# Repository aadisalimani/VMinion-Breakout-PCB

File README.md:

# VMinion Breakout PCB

This project is focused on creating a PCB that simplifies connections on the Ratrig VMinion. Although designed be me, it is inspired by the divider PCB mod by Vector3D [here](https://github.com/AdamV3D/RR-V-Minion-Mods/tree/main/V3D%20Divider%20PCB). 

## :warning: Beta Version :warning:
Please note that the "VMinion Breakout PCB" is currently in a **beta phase**. It's constantly being updated and improved. Use this mod at your own risk. The rest of the parts (printed casing, mounting parts, etc.) will come soon.

## Open Source
Everything related to this project will be open-source. Contributions, suggestions, and improvements are always welcome.

## Bill of Materials (BOM)
A work-in-progress BOM is available [here](https://docs.google.com/spreadsheets/d/1l2unTY74QwLAbzYWbJA4JIBaFDDriVfRlH6mz4mGnKs/edit?usp=sharing).

## Getting Started
*Features*

Unlike other breakout boards, this has a plethora of ports to fit almost any configuration:

- 4x Motor Ports
- 5x General Ports (Endstop, Servo, Neopixel etc.)
- 1x Probe Port (5v or 24v with diode)
- 3x Fan Ports (Selectable Voltage) - Two Ports Share Selected Voltage
- 1x ADXL Port
- 2x Therm Ports
- 1x Hotend Port (Max ~120W)
- 1x Bed Port (Max ~180W)
- 1x 24v Step Down To 12v (K78L12-500R3)

Uses 2x 2x9 Microfit And 1x Plugable Terminal Block

*Instrucions will follow soon*

## PCB Images

## License
This PCB project is licensed under the Creative Commons Attribution-NonCommercial 4.0 International License - see the [LICENSE](LICENSE) file for details.

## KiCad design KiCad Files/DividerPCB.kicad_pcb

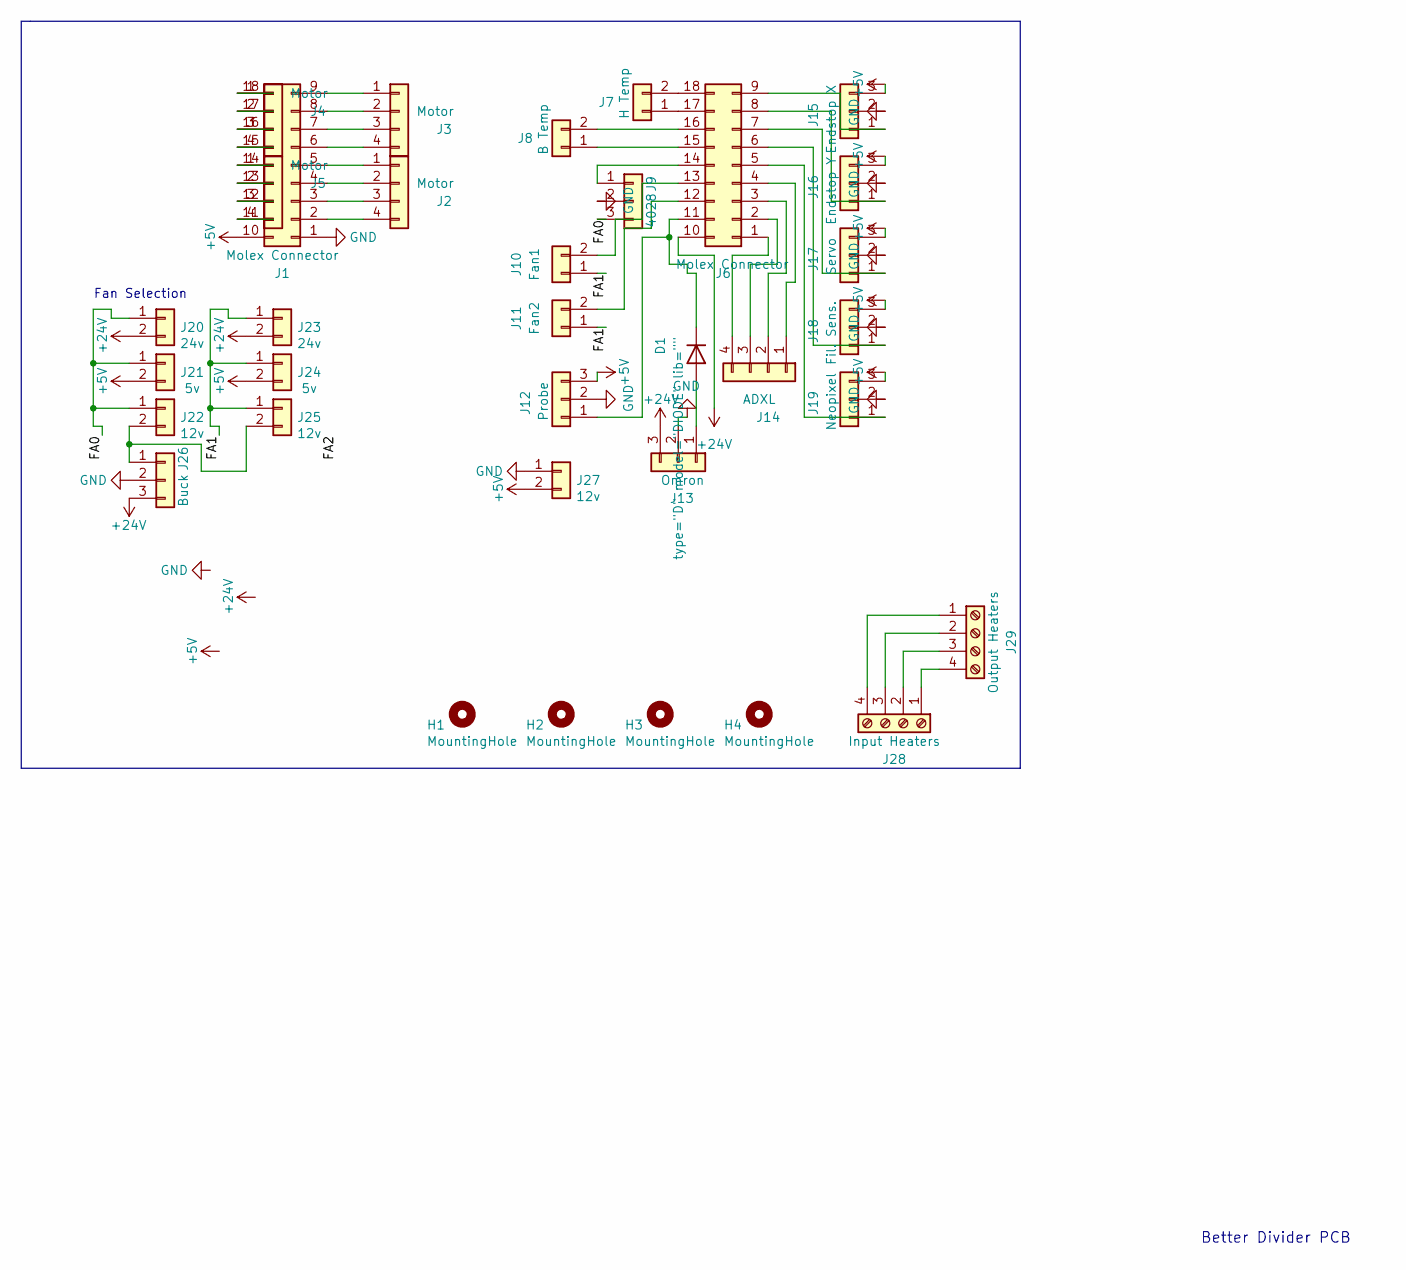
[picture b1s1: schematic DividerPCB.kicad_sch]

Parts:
D1: type="D" model="DIODE" lib=""; D_DO-35_SOD27_P7.62mm_Horizontal
H1, H2, H3, H4: MountingHole; MountingHole_3.2mm_M3_Pad_Via
J1, J6: Molex Connector; Molex_Micro-Fit_3.0_43045-1800_2x09_P3.00mm_Horizontal
J2, J3, J4, J5: Motor; JST_XH_B4B-XH-A_1x04_P2.50mm_Vertical
J7: H Temp; JST_XH_B2B-XH-A_1x02_P2.50mm_Vertical
J8: B Temp; JST_XH_B2B-XH-A_1x02_P2.50mm_Vertical
J9: 4028; JST_XH_B3B-XH-A_1x03_P2.50mm_Vertical
J10: Fan1; JST_XH_B2B-XH-A_1x02_P2.50mm_Vertical
J11: Fan2; JST_XH_B2B-XH-A_1x02_P2.50mm_Vertical
J12: Probe; JST_XH_B3B-XH-A_1x03_P2.50mm_Vertical
J13: Omron; PinHeader_1x03_P2.54mm_Vertical
J14: ADXL; PinHeader_1x04_P2.54mm_Vertical
J15: Endstop X; JST_XH_B3B-XH-A_1x03_P2.50mm_Vertical
J16: Endstop Y; JST_XH_B3B-XH-A_1x03_P2.50mm_Vertical
J17: Servo; JST_XH_B3B-XH-A_1x03_P2.50mm_Vertical
J18: Fil. Sens.; JST_XH_B3B-XH-A_1x03_P2.50mm_Vertical
J19: Neopixel; JST_XH_B3B-XH-A_1x03_P2.50mm_Vertical
J20, J23: 24v; PinHeader_1x02_P2.54mm_Vertical
J21, J24: 5v; PinHeader_1x02_P2.54mm_Vertical
J22, J25, J27: 12v; PinHeader_1x02_P2.54mm_Vertical
J26: Buck; PinHeader_1x03_P2.54mm_Vertical
J28: Input Heaters; 2EDGR-5.0-04P-14-00AH_DEG
J29: Output Heaters; TerminalBlock_Phoenix_MKDS-1,5-4_1x04_P5.00mm_Horizontal_Mod

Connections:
+5V: J1.10, J12.3, J15.3, J16.3, J17.3, J18.3, J19.3, J21.2, J24.2, J27.2
+24V: J6.10, J13.3, J20.2, J23.2, J26.3
/FA0: J9.3, J20.1, J21.1, J22.1
/FA1: J10.1, J11.1, J23.1, J24.1, J25.1
GND: J1.1, J9.2, J12.2, J13.2, J15.2, J16.2, J17.2, J18.2, J19.2, J26.2, J27.1
unnamed: D1.1 (A), J13.1
unnamed: D1.2 (K), J6.11, J12.1
unnamed: J1.2, J2.4
unnamed: J1.3, J2.3
unnamed: J1.4, J2.2
unnamed: J1.5, J2.1
unnamed: J1.6, J3.4
unnamed: J1.7, J3.3
unnamed: J1.8, J3.2
unnamed: J1.9, J3.1
unnamed: J1.11, J5.4
unnamed: J1.12, J5.3
unnamed: J1.13, J5.2
unnamed: J1.14, J5.1
unnamed: J1.15, J4.4
unnamed: J1.16, J4.3
unnamed: J1.17, J4.2
unnamed: J1.18, J4.1
unnamed: J6.14, J9.1
unnamed: J6.15, J8.1
unnamed: J6.16, J8.2
unnamed: J6.17, J7.1
unnamed: J6.18, J7.2
unnamed: J6.13, J10.2
unnamed: J6.12, J11.2
unnamed: J6.4, J14.1
unnamed: J6.3, J14.2
unnamed: J6.2, J14.3
unnamed: J6.1, J14.4
unnamed: J6.9, J15.1
unnamed: J6.8, J16.1
unnamed: J6.7, J17.1
unnamed: J6.6, J18.1
unnamed: J6.5, J19.1
unnamed: J22.2, J25.2, J26.1
unnamed: J28.1, J29.4
unnamed: J28.2, J29.3
unnamed: J28.3, J29.2
unnamed: J28.4, J29.1

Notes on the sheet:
Fan Selection
Better Divider PCB

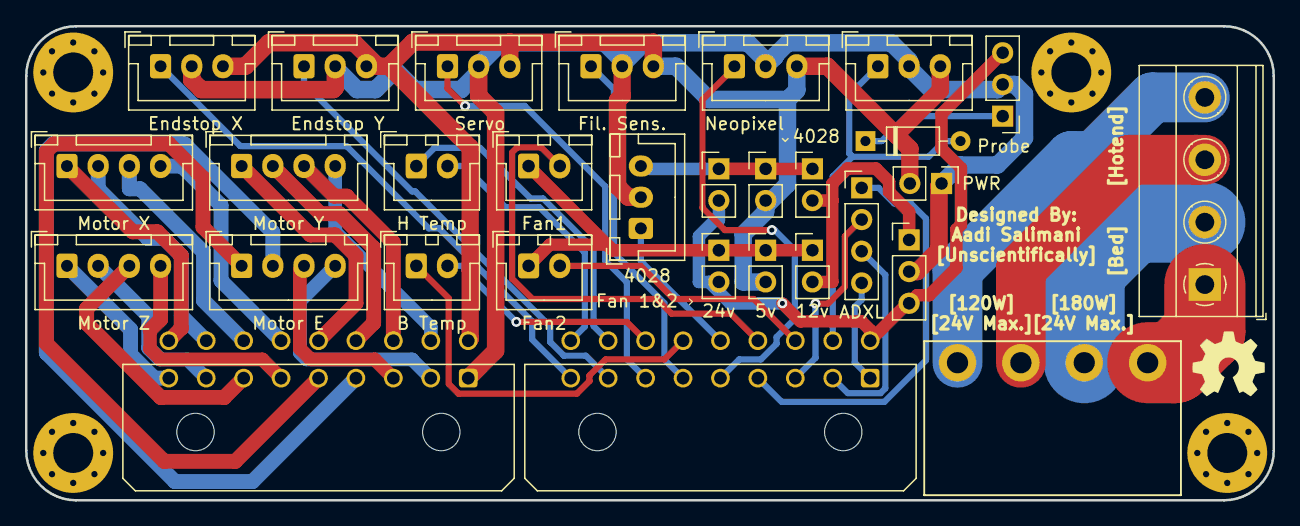
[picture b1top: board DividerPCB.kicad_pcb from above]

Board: 2 copper layers, 100.0 x 38.0 mm, 36 parts (1 on the bottom side), 44 nets.

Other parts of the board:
Garfield: LOGO; sleeping
Open: LOGO; open

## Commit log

2023-11-23 Create KiCad Stuff
2023-11-23 Update KiCad Stuff
2023-11-23 Create Description
2023-11-23 Create LICENSE
